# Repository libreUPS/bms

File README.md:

# bms (now in work)
Battery management system

In this repository you will find the `battery management system` for the [libreUPS](https://github.com/libreUPS) complex.

# Notes for `bms`

Board components:
- asic: BQ7694003DBT(C368606) [BQ76952]
- mcu: STM32xxxx
- Fuse: -
- Interface: RS485 and CAN

Target: 15S

https://www.aliexpress.com/item/1005005429173167.html

# Credit
## Array Cells
BQ769x0:
[sparkfan-bms](https://github.com/nseidle/BMS)

[BMS48V](https://github.com/LibreSolar/bms-15s80-sc)

[BMS Design with BQ76940](https://github.com/fatihbyrmn/BQ7694-IC)

[BQ76920-BMS](https://github.com/ceech/BQ76920-BMS)

[18V 20A LiPO Li-ion battery management system BMS](https://www.tindie.com/products/ceech/18v-20a-lipo-li-ion-battery-management-system-bms/#)

[bq76920_board](https://github.com/ealex/bq76920_board)

[bq76930_board](https://github.com/ealex/bq76930_board)

[bms-nrf](https://github.com/scttnlsn/bms)

LTC6802:
[openBMS](https://github.com/rickygu/openBMS)

industrial:
[ENNOID](https://github.com/EnnoidMe/ENNOID-BMS)

[foxbms](https://github.com/foxBMS/foxbms)

## Singl Cells
[SmartBMS](https://github.com/Green-bms/SmartBMS)

[diyBMSv4](https://github.com/stuartpittaway/diyBMSv4)

## Other
[VESC BMS](https://github.com/vedderb/vesc_bms_fw)

[LiFePO4_balancer (no smart)](https://oshwlab.com/efkostya/lifepo4_balancer)

https://www.farnell.com/datasheets/2036067.pdf

https://www.ti.com/lit/pdf/SLUA769

https://www.ti.com/lit/pdf/SLUA749

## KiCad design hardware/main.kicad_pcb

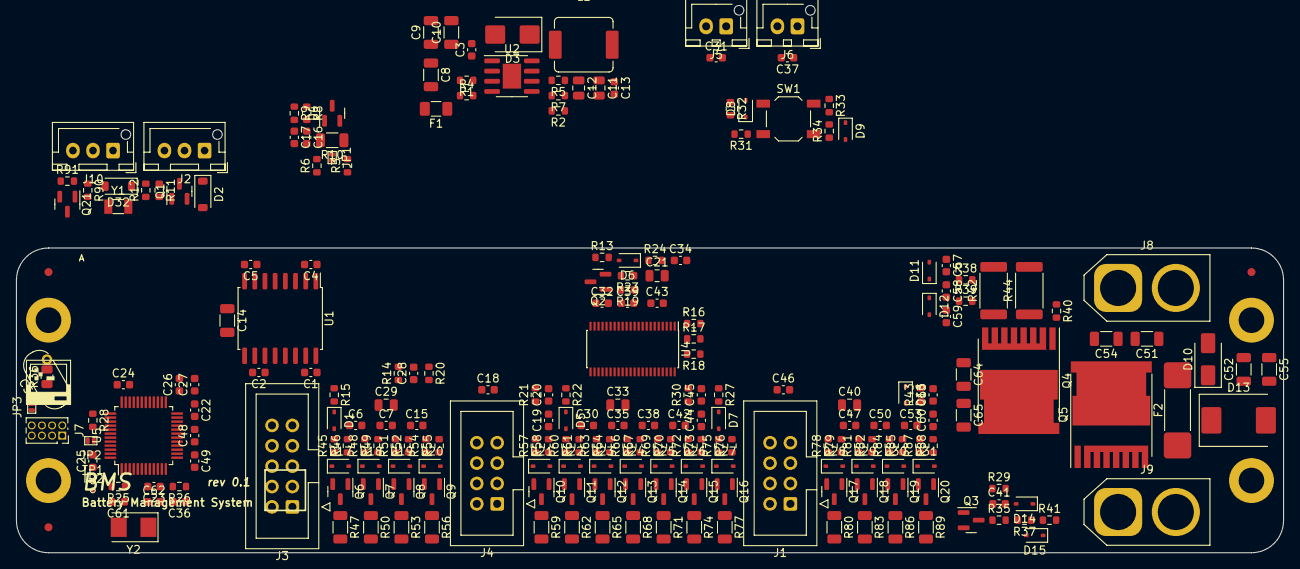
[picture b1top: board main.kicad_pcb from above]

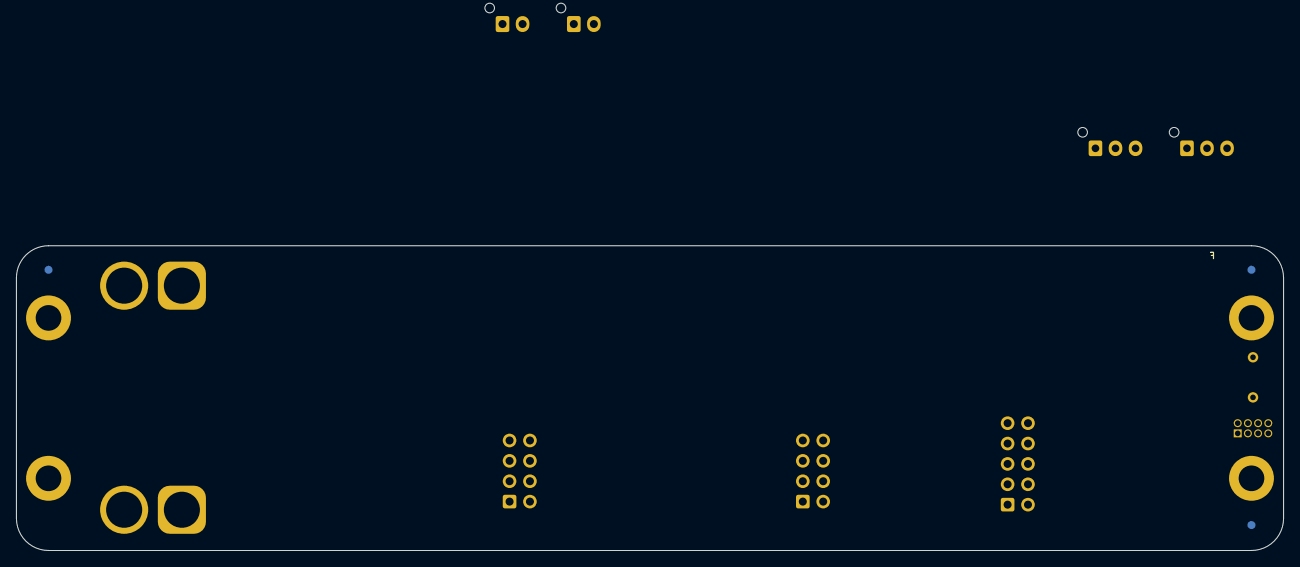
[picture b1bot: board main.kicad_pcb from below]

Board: 2 copper layers, 158.0 x 38.0 mm, 244 parts (3 on the bottom side), 143 nets, no tracks yet.

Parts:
C1, C3, C4, C13, C22, C23, C24, C25, C26, C27, C28, C36, C57, C58, C59: 100n; C_0603_1608Metric
C2, C5: 10u; C_0603_1608Metric
C6, C7, C15, C18, C19, C20, C30, C32, C34, C35, C38, C39, C42, C43, C44, C45, C46, C47, C50, C53, C60, C63: 1u; C_0603_1608Metric
C8, C9, C10: 2.2u; C_1206_3216Metric
C11, C12, C21: 22u; C_0805_2012Metric
C14: 1n (-); C_1206_3216Metric
C16, C17: 330p; C_0603_1608Metric
C29, C33, C40: 10u; C_0805_2012Metric
C31, C37, C41: 1n; C_0603_1608Metric
C48, C49, C61, C62: 12p; C_0603_1608Metric
C51, C52, C54, C55, C64, C65: 100n; C_1206_3216Metric
C56: JYC3D332MBF
D1, D5, D6, D7, D8, D14: 1N4148WS; D_SOD-323
D2, D32: MBR0540; D_SOD-123
D3: STPS2L40U; D_SMB
D4: PESD1CAN; SOT-23
D9, D11, D12, D16: BZT52C3V3; D_SOD-323
D10: SMCJ75A; D_SMA
D13: ER3J; D_SMC
D15: BZT52C16SQ; D_SOD-323
D17, D18, D19, D20, D21, D22, D23, D24, D25, D26, D27, D28, D29, D30, D31: BZT52C5V6S; D_SOD-323
F1: 12T.30000063AG12S1B02; Fuse_1206_3216Metric
F2: S1032-F-40.0A; Fuse_1032
FID1, FID2, FID3, FID4, FID5, FID6: F; Fiducial_1mm_Mask3mm
H1, H2, H3, H4: H; MountingHole_3.2mm_M3_DIN965_Pad
J1, J4: IDC-08M; IDC-Header_2x04_P2.54mm_Vertical
J2, J10: B3B-XH-A; JST_XH_B3B-XH-AM_1x03_P2.50mm_Vertical
J3: DS1013-10S; IDC-Header_2x05_P2.54mm_Vertical
J5, J6: B2B-XH-A; JST_XH_B2B-XH-AM_1x02_P2.50mm_Vertical
J7: IDC-08M; PinSocket_2x04_P1.27mm_Vertical
J8, J9: XT60; AMASS_XT60-F_1x02_P7.20mm_Vertical
JP1: Jload; SolderJumper_Open_Pad0.5x0.8mm
JP2: BOOT; SolderJumper_Open_Pad0.5x0.8mm
JP3: PWRprog; SolderJumper_Open_Pad0.5x0.8mm
L1: SMMS0650-100M; SMDL_7.1x6.6x5mm
Q1, Q2, Q21: 5N10-MS; SOT-23
Q3: AO3401A; SOT-23
Q4, Q5: IPT007N06N; Infineon_PG-HSOF-8-1
Q6, Q7, Q8, Q9, Q10, Q11, Q12, Q13, Q14, Q15, Q16, Q17, Q18, Q19, Q20: IRLML6402; SOT-23
R1, R8, R9, R11, R15, R22, R24, R25, R27, R38, R39, R90: 100R; R_0603_1608Metric
R2, R12, R14, R19, R23, R91: 100k; R_0603_1608Metric
R3, R6: 0R; R_0603_1608Metric
R4: 47k; R_0603_1608Metric
R5, R7: 18k; R_0603_1608Metric
R10: 120R; R_1206_3216Metric
R13: 200R; R_0603_1608Metric
R16, R17, R46, R49, R52, R55, R58, R61, R64, R67, R70, R73, R76, R79, R82, R85, R88: 10k; R_0603_1608Metric
R18, R37, R40, R41: 1M; R_0603_1608Metric
R20: 5.6k; R_0603_1608Metric
R21, R30, R31, R35, R43, R45, R48, R51, R54, R57, R60, R63, R66, R69, R72, R75, R78, R81, R84, R87: 1k; R_0603_1608Metric
R26, R28, R32, R33: 4.7k; R_0603_1608Metric
R29: 10k/NTC; R_0603_1608Metric
R34: 51k; R_0603_1608Metric
R36: 10M; R_0805_2012Metric
R42, R44: 3m; R_2512_6332Metric
R47, R50, R53, R56, R59, R62, R65, R68, R71, R74, R77, R80, R83, R86, R89: 100R; R_1206_3216Metric
SW1: TS-1187A-B-A-B; SW_SPST_TL3342
TP1: SCL; TestPoint_Pad_D0.5mm
TP2: SDA; TestPoint_Pad_D0.5mm
U1: CA-IS3062W; SOIC-16W_7.5x10.3mm_P1.27mm
U2: LMR16030SDDAR; SOIC-8-1EP_3.9x4.9mm_P1.27mm_EP2.29x3mm
U4: BQ7694003DBT; TSSOP-44_4.4x11.2mm_P0.5mm
U5: STM32F103C8Tx; LQFP-48_7x7mm_P0.5mm
Y1: NX3215SA-32.768; Crystal_SMD_3215-2Pin_3.2x1.5mm
Y2: X50328MSB2GI; Crystal_SMD_5032-2Pin_5.0x3.2mm

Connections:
+3.3V: C4.1, C5.1, C21.1, C22.1, C23.1, C24.1, C25.1, C26.1, C27.1, JP2.2 (B), JP3.2 (B), R16.2, R17.2, R25.2, R26.2, U1.1 (VDD1), U4.8 (REGOUT), U5.9 (VDDA), U5.24 (VDD), U5.36 (VDD), U5.48 (VDD)
+5V: C11.1, C12.1, C13.1, D2.1 (K), D32.1 (K), J2.1, J10.1, L1.2, R2.1
/ALERT: R18.2, U4.44 (ALERT), U5.41 (PB5)
/B0: C63.2, D16.1 (K), R43.2, U4.41 (VC0)
/B1: C53.2, C60.1, R31.2, R87.2, R88.2, U4.40 (VC1)
/B2: C50.2, C53.1, R84.2, R85.2, U4.39 (VC2)
/B3: C47.2, C50.1, R81.2, R82.2, U4.38 (VC3)
/B4: C46.2, C47.1, R78.2, R79.2, U4.37 (VC4)
/B5: C46.1, D7.2 (A), R75.2, R76.2, U4.36 (VC5)
/B5b: C45.2, R30.2, U4.35 (VC5B)
/B6: C42.2, C44.1, R72.2, R73.2, U4.34 (VC6)
/B7: C38.2, C42.1, R69.2, R70.2, U4.33 (VC7)
/B8: C35.2, C38.1, R66.2, R67.2, U4.32 (VC8)
/B9: C30.2, C35.1, R63.2, R64.2, U4.31 (VC9)
/B10: C30.1, D5.2 (A), R60.2, R61.2, U4.30 (VC10)
/B10b: C20.2, R21.2, U4.29 (VC10B)
/B11: C18.2, C19.1, R57.2, R58.2, U4.28 (VC11)
/B12: C15.2, C18.1, R54.2, R55.2, U4.27 (VC12)
/B13: C7.2, C15.1, R51.2, R52.2, U4.26 (VC13)
/B14: C6.2, C7.1, R48.2, R49.2, U4.25 (VC14)
/B15: C6.1, D1.2 (A), R45.2, R46.2, U4.24 (VC15)
/BAT: C29.1, D1.1 (K), R15.2, U4.20 (BAT)
/BAT+: C51.1, C52.1, D10.1 (A1), D13.1 (K), D17.1 (K), F1.2, F2.2, J4.8, J8.2, Q6.2 (S), R13.1, R14.2, R15.1, R45.1
/BOOT0: JP2.1 (A), R28.2, U5.44 (BOOT0)
/BTN: D9.1 (K), R33.2, R34.2, U5.40 (PB4)
/C1: D31.1 (K), J1.2, Q20.2 (S), R86.2, R87.1
/C2: D30.1 (K), J1.3, Q19.2 (S), R83.2, R84.1
/C3: D29.1 (K), J1.4, Q18.2 (S), R80.2, R81.1
/C4: D28.1 (K), J1.5, Q17.2 (S), R77.2, R78.1
/C5: D27.1 (K), J1.6, Q16.2 (S), R27.1, R30.1, R74.2, R75.1
/C6: D26.1 (K), J1.7, Q15.2 (S), R71.2, R72.1
/C7: D25.1 (K), J1.8, Q14.2 (S), R68.2, R69.1
/C8: D24.1 (K), J4.1, Q13.2 (S), R65.2, R66.1
/C9: D23.1 (K), J4.2, Q12.2 (S), R62.2, R63.1
/C10: D22.1 (K), J4.3, Q11.2 (S), R21.1, R22.1, R59.2, R60.1
/C11: D21.1 (K), J4.4, Q10.2 (S), R56.2, R57.1
/C12: D20.1 (K), J4.5, Q9.2 (S), R53.2, R54.1
/C13: D19.1 (K), J4.6, Q8.2 (S), R50.2, R51.1
/C14: D18.1 (K), J4.7, Q7.2 (S), R47.2, R48.1
/CANH: J3.7, R3.1
/CANL: J3.8, R6.1
/CANgnd: C1.2, C2.2, C14.2, C16.2, C17.2, D4.3 (A), J3.9, U1.9 (GND2), U1.10 (GND2), U1.15 (GND2)
/CANrx: U1.5 (RxD), U5.32 (PA11)
/CANtx: U1.3 (TxD), U5.33 (PA12)
/CANvcc: C1.1, C2.1, J3.10, U1.11 (VDD2), U1.16 (VDD2)
/CHG: Q3.2 (S), U4.1 (DSG)
/DBG_RX: J7.5, U5.31 (PA10)
/DBG_TX: J7.6, U5.30 (PA9)
/DSG: Q4.1 (G), R40.2, U4.2 (CHG)
/EN5V: R1.2, U5.38 (PA15)
/HSE_IN: C62.1, U5.5 (PD0), Y2.1
/HSE_OUT: C61.1, U5.6 (PD1), Y2.2
/IO1: J3.3, U5.25 (PB12)
/IO2: J3.4, U5.26 (PB13)
/IO3: J3.5, U5.27 (PB14)
/IO4: R11.2, R90.2, U5.28 (PB15)
/K1: J3.1, R31.1, SW1.2
/K2: D8.2 (A), J3.2, R33.1, SW1.1
/LSE_IN: C49.1, U5.14 (PA4), Y1.1
/LSE_OUT: C48.1, U5.15 (PA5), Y1.2
/NRST: C36.1, J7.7, R26.1, U5.7 (NRST)
/PACK+: F2.1, J9.2
/PACK-: C55.2, C65.2, D13.2 (A), D15.2 (A), J9.1, Q5.2 (S), R41.1
/REGSRC: C34.1, R24.2, U4.9 (REGSRC)
/SCL: R17.1, TP1.1, U4.5 (SCL), U5.42 (PB6)
/SDA: R16.1, TP2.1, U4.4 (SDA), U5.43 (PB7)
/SRN: C58.2, C59.1, D12.1 (K), R39.1, U4.43 (SRN)
/SRP: C57.2, C58.1, D11.1 (K), R38.1, U4.42 (SRP)
/SYS_SWCLK: J7.4, U5.37 (PA14)
/SYS_SWDIO: J7.3, U5.34 (PA13)
/SYS_SWO: J7.2, U5.39 (PB3)
/VC5x: C33.2, C37.2, C39.2, C40.1, C44.2, C45.1, D7.1 (K), J6.2, R19.1, R27.2, U4.10 (VC5X)
/VC10x: C19.2, C20.1, C29.2, C31.1, C32.2, C33.1, D5.1 (K), J5.2, R22.2, U4.15 (VC10X)
/V_BAT: C28.1, R14.1, R20.2, U5.10 (PA0)
GND: C4.2, C5.2, C8.2, C9.2, C10.2, C11.2, C12.2, C13.2, C14.1, C21.2, C22.2, C23.2, C24.2, C25.2, C26.2, C27.2, C28.2, C34.2, C36.2, C40.2, C41.2, C43.2, C48.2, C49.2, C54.2, C56.1, C57.1, C59.2, C60.2, C61.2, C62.2, C63.1, D3.2 (A), D9.2 (A), D10.2 (A2), D11.2 (A), D12.2 (A), D16.2 (A), J1.1, J2.3, J3.6, J7.1, J8.1, J10.3, Q1.2 (S), Q3.1 (G), Q21.2 (S), R4.1, R5.1, R7.1, R12.1, R18.1, R20.1, R28.1, R29.2, R34.1, R36.1, R38.2, R42.2, R43.1, R44.2, R89.2, R91.1, U1.2 (GND1), U1.8 (GND1), U2.7 (GND), U2.9 (GND), U4.3 (VSS), U5.8 (VSSA), U5.23 (VSS), U5.35 (VSS), U5.47 (VSS)
GNDREF: C56.2, H4.1, R36.2
unnamed: C16.1, R8.2
unnamed: C17.1, R9.2
unnamed: C51.2, C54.1
unnamed: C52.2, C55.1
unnamed: C64.2, C65.1
unnamed: D2.2 (A), J2.2, Q1.3 (D)
unnamed: C3.2, D3.1 (K), L1.1, U2.8 (SW)
unnamed: D6.2 (A), Q2.2 (S), R23.2
unnamed: D6.1 (K), R23.1, R24.1
unnamed: D8.1 (K), R32.2
unnamed: D14.2 (A), R35.2, R37.2
unnamed: D14.1 (K), D15.1 (K), Q5.1 (G), R37.1, R41.2
unnamed: D17.2 (A), Q6.1 (G), R46.1
unnamed: D18.2 (A), Q7.1 (G), R49.1
unnamed: D19.2 (A), Q8.1 (G), R52.1
unnamed: D20.2 (A), Q9.1 (G), R55.1
unnamed: D21.2 (A), Q10.1 (G), R58.1
unnamed: D22.2 (A), Q11.1 (G), R61.1
unnamed: D23.2 (A), Q12.1 (G), R64.1
unnamed: D24.2 (A), Q13.1 (G), R67.1
unnamed: D25.2 (A), Q14.1 (G), R70.1
unnamed: D26.2 (A), Q15.1 (G), R73.1
unnamed: D27.2 (A), Q16.1 (G), R76.1
unnamed: D28.2 (A), Q17.1 (G), R79.1
unnamed: D29.2 (A), Q18.1 (G), R82.1
unnamed: D30.2 (A), Q19.1 (G), R85.1
unnamed: D31.2 (A), Q20.1 (G), R88.1
unnamed: D32.2 (A), J10.2, Q21.3 (D)
unnamed: C31.2, J5.1, U4.18 (TS3)
unnamed: C37.1, J6.1, U4.13 (TS2)
unnamed: J7.8, JP3.1 (A)
unnamed: JP1.1 (A), R10.1
unnamed: D4.2 (K), JP1.2 (B), R3.2, R9.1, U1.13 (H)
unnamed: Q1.1 (G), R11.1, R12.2
unnamed: Q2.3 (D), R13.2
unnamed: Q2.1 (G), R19.2
unnamed: Q3.3 (D), R35.1
unnamed: Q4.3 (D), Q5.3 (D)
unnamed: C64.1, Q4.2 (S), R39.2, R40.1, R42.1, R44.1
unnamed: Q6.3 (D), R47.1
unnamed: Q7.3 (D), R50.1
unnamed: Q8.3 (D), R53.1
unnamed: Q9.3 (D), R56.1
unnamed: Q10.3 (D), R59.1
unnamed: Q11.3 (D), R62.1
unnamed: Q12.3 (D), R65.1
unnamed: Q13.3 (D), R68.1
unnamed: Q14.3 (D), R71.1
unnamed: Q15.3 (D), R74.1
unnamed: Q16.3 (D), R77.1
unnamed: Q17.3 (D), R80.1
unnamed: Q18.3 (D), R83.1
unnamed: Q19.3 (D), R86.1
unnamed: Q20.3 (D), R89.1
unnamed: Q21.1 (G), R90.1, R91.2
unnamed: D4.1 (K), R6.2, R8.1, R10.2, U1.12 (L)
unnamed: C3.1, U2.1 (BOOT)
unnamed: R1.1, U2.3 (EN)
unnamed: R2.2, R7.2, U2.5 (FB)
unnamed: R4.2, U2.4 (RT/CLK)
unnamed: R5.2, U2.6 (SS/PG)
unnamed: C8.1, C9.1, C10.1, F1.1, U2.2 (VIN)
unnamed: C43.1, U4.7 (CAP1)
unnamed: C39.1, U4.11 (NC(CAP2)), U4.12 (NC(CAP2)), U4.14 (CAP2)
unnamed: C32.1, U4.16 (NC(CAP3)), U4.17 (NC(CAP3)), U4.19 (CAP3)
unnamed: C41.1, R29.1, R32.1, U4.6 (TS1)
unnamed: R25.1, U5.1 (VBAT)

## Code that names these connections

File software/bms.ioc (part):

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Mcu.Name=STM32F103C(8-B)Tx
Mcu.Package=LQFP48
Mcu.UserName=STM32F103C8Tx
PA0-WKUP.Signal=ADCx_IN0
PA10.Mode=Asynchronous
PA10.Signal=USART1_RX
PA11.Mode=CAN_Activate
PA11.Signal=CAN_RX
PA12.Mode=CAN_Activate
PA12.Signal=CAN_TX
PA13.Mode=Trace_Asynchronous_SW
PA13.Signal=SYS_JTMS-SWDIO
PA14.Mode=Trace_Asynchronous_SW
PA14.Signal=SYS_JTCK-SWCLK
PA15.Signal=GPIO_Output
PA9.Mode=Asynchronous
PA9.Signal=USART1_TX
PB12.Signal=GPIO_Output
PB13.Signal=GPIO_Output
PB14.Signal=GPIO_Output
PB15.Signal=GPIO_Output
PB3.Mode=Trace_Asynchronous_SW
PB3.Signal=SYS_JTDO-TRACESWO
PB4.Signal=GPIO_Input
PB5.Signal=GPIO_Input
PB6.Mode=I2C
PB6.Signal=I2C1_SCL
PB7.Mode=I2C
PB7.Signal=I2C1_SDA
PC14-OSC32_IN.Mode=LSE-External-Oscillator
PC14-OSC32_IN.Signal=RCC_OSC32_IN
PC15-OSC32_OUT.Mode=LSE-External-Oscillator
PC15-OSC32_OUT.Signal=RCC_OSC32_OUT
PD0-OSC_IN.Mode=HSE-External-Clock-Source
PD0-OSC_IN.Signal=RCC_OSC_IN
PD1-OSC_OUT.Mode=HSE-External-Clock-Source
PD1-OSC_OUT.Signal=RCC_OSC_OUT
board=custom

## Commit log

2023-06-16 clean prj
2023-06-23 created sсh
2023-06-25 finish sch
2023-06-25 init pcb
2023-06-25 update prj
2023-06-26 update pcb
2023-10-01 update can
2023-10-22 fix prj; description -> Comments
